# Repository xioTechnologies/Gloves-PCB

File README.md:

Gloves-PCB
==========

Temporary PCB solution for [the gloves](http://theglovesproject.com/).  Design include five separate PCBs: one main board, two LED boards and two vibration motor boards.  The main board mounts an [x-OSC](http://www.x-io.co.uk/products/x-osc/) an [x-BIMU](http://www.x-io.co.uk/products/x-bimu/) and features an LED bar graph to indicate battery level using the [LM3914](https://www.sparkfun.com/products/12694).  More information available on [blog post](http://theglovesproject.com/breakout-board-for-nime/).

Images
------

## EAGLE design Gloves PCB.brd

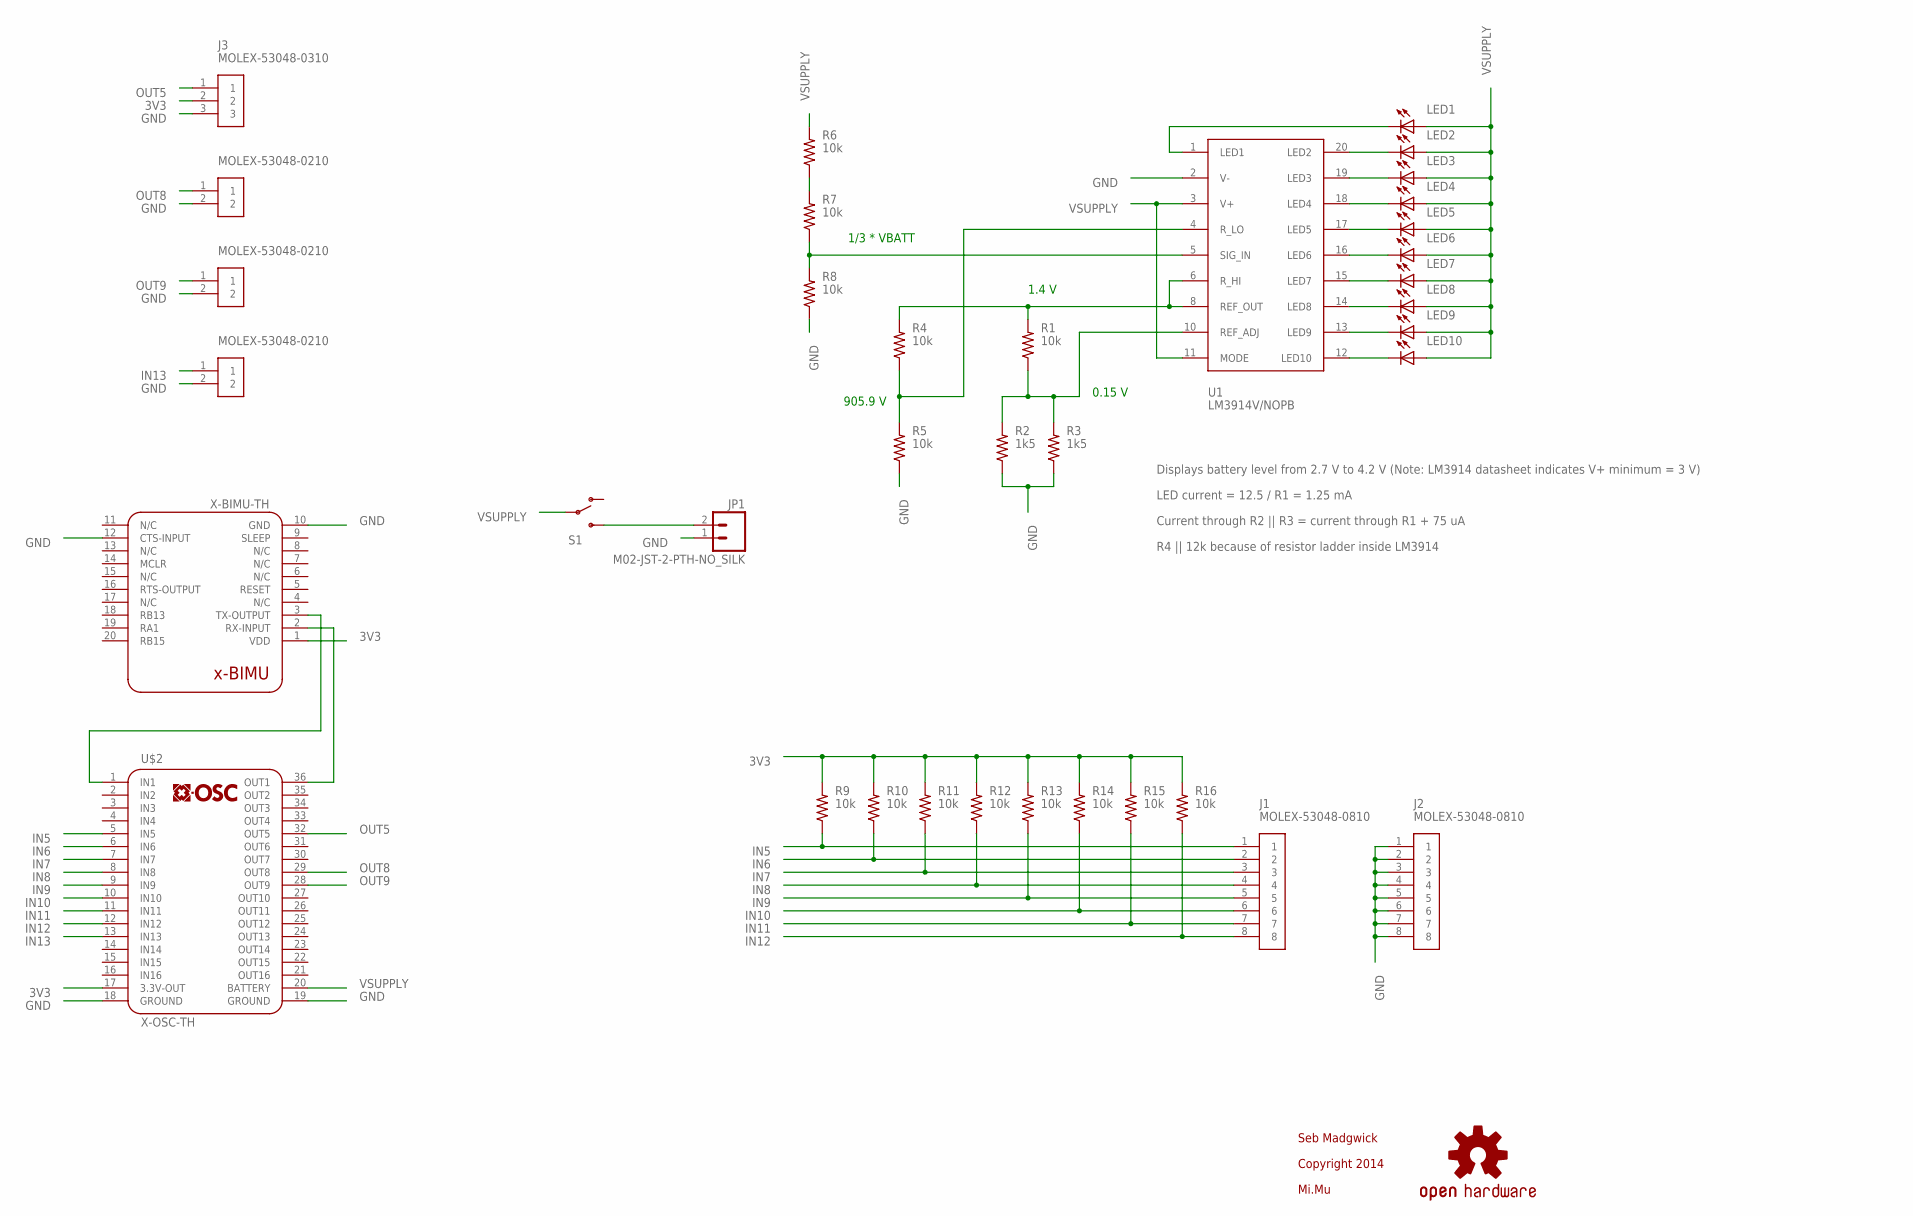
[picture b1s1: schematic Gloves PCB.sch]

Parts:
J1, J2: MOLEX-53048-0810
J3: MOLEX-53048-0310
J4, J5, J6: MOLEX-53048-0210
JP1: M02-JST-2-PTH-NO_SILK; JST-2-PTH-NS
LED1, LED2, LED3, LED4, LED5, LED6, LED7, LED8, LED9, LED10: LEDCHIPLED_1206; CHIPLED_1206
R1, R4, R5, R6, R7, R8, R9, R10, R11, R12, R13, R14, R15, R16: 10k; 0805
R2, R3: 1k5; 0805
S1: SWITCH-DPST; WURTH-ELEKTRONIK-450301014042
U1: LM3914V/NOPB; PLCC-20
U$1: OSHW-LOGOS; OSHW-LOGO-S
U$2: X-OSC-TH; X-OSC_TH
U$3: X-BIMU-TH; X-BIMU_TH

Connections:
3V3: J3.2, R9.2, R10.2, R11.2, R12.2, R13.2, R14.2, R15.2, R16.2, U$2.17 (3.3V-OUT), U$3.1 (VDD)
GND: J2.1, J2.2, J2.3, J2.4, J2.5, J2.6, J2.7, J2.8, J3.3, J4.2, J5.2, J6.2, JP1.1, R2.1, R3.1, R5.1, R8.1, U1.2 (V-), U$2.18 (GROUND), U$2.19 (GROUND), U$3.10 (GND), U$3.12 (CTS-INPUT)
IN5: J1.1, R9.1, U$2.5 (IN5)
IN6: J1.2, R10.1, U$2.6 (IN6)
IN7: J1.3, R11.1, U$2.7 (IN7)
IN8: J1.4, R12.1, U$2.8 (IN8)
IN9: J1.5, R13.1, U$2.9 (IN9)
IN10: J1.6, R14.1, U$2.10 (IN10)
IN11: J1.7, R15.1, U$2.11 (IN11)
IN12: J1.8, R16.1, U$2.12 (IN12)
IN13: J6.1, U$2.13 (IN13)
unnamed: U$2.1 (IN1), U$3.3 (TX-OUTPUT)
unnamed: R4.1, R5.2, U1.4 (R_LO)
unnamed: JP1.2, S1.3
unnamed: R7.1, R8.2, U1.5 (SIG_IN)
unnamed: R6.1, R7.2
unnamed: R1.1, R2.2, R3.2, U1.10 (REF_ADJ)
unnamed: LED10.C, U1.12 (LED10)
unnamed: LED9.C, U1.13 (LED9)
unnamed: LED8.C, U1.14 (LED8)
unnamed: LED7.C, U1.15 (LED7)
unnamed: LED6.C, U1.16 (LED6)
unnamed: LED5.C, U1.17 (LED5)
unnamed: LED4.C, U1.18 (LED4)
unnamed: LED3.C, U1.19 (LED3)
unnamed: LED2.C, U1.20 (LED2)
unnamed: LED1.C, U1.1 (LED1)
unnamed: U$2.36 (OUT1), U$3.2 (RX-INPUT)
OUT5: J3.1, U$2.32 (OUT5)
OUT8: J4.1, U$2.29 (OUT8)
OUT9: J5.1, U$2.28 (OUT9)
REF_OUT: R1.2, R4.2, U1.6 (R_HI), U1.8 (REF_OUT)
VSUPPLY: LED1.A, LED2.A, LED3.A, LED4.A, LED5.A, LED6.A, LED7.A, LED8.A, LED9.A, LED10.A, R6.2, S1.2, U1.3 (V+), U1.11 (MODE), U$2.20 (BATTERY)

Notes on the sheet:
Seb Madgwick
1.4 V
0.15 V
905.9 V
Displays battery level from 2.7 V to 4.2 V (Note: LM3914 datasheet indicates V+ minimum = 3 V)
1/3 * VBATT
LED current = 12.5 / R1 = 1.25 mA
Current through R2 || R3 = current through R1 + 75 uA
R4 || 12k because of resistor ladder inside LM3914
Copyright 2014
Mi.Mu

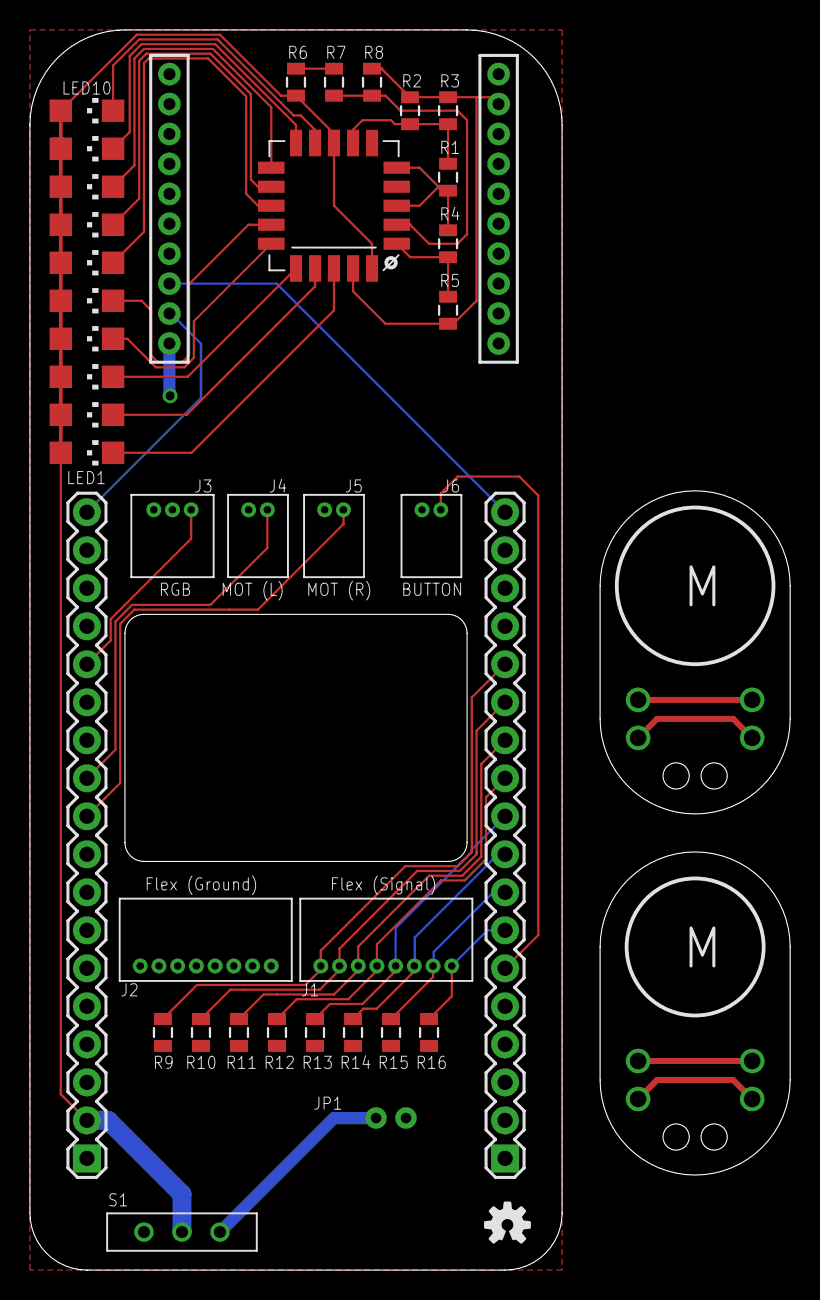
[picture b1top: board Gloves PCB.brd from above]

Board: 2 copper layers, 50.8 x 82.9 mm, 38 parts (0 on the bottom side), 33 nets.

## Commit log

2014-04-14 Add project files
2014-04-24 Add photos
2014-08-31 v1.1 commit
2014-09-03 Update Eagle screenshot
2014-09-12 Add photo of v1.1
2014-09-29 Commit BOM
2014-10-30 Add motor board files with larger strain relief holes

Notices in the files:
parts and their libraries:
SparkFun_08_2011: Licensing: CC v3.0 Share-Alike You are welcome to use this library for commercial purposes.
SparkFun-Passives: Licensing: Creative Commons ShareAlike 4.0 International - https://creativecommons.org/licenses/by-sa/4.0
